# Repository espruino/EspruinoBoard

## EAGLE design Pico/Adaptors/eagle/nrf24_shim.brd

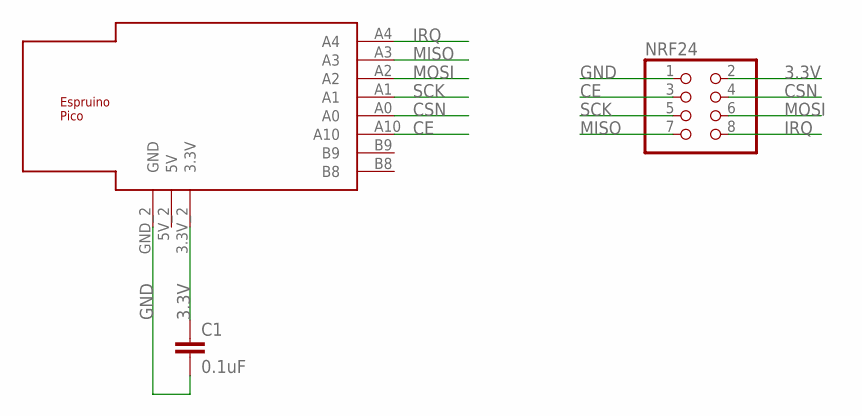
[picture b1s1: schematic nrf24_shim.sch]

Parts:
C1: 0.1uF; C1206
NRF24: PINHD-2X4; 2X04
U$1: ESPRUINO_PICO_0.05_SMALL

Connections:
3.3V: C1.1, NRF24.2, U$1.3.3V_2 (3.3V)
CE: NRF24.3, U$1.A10
CSN: NRF24.4, U$1.A0
GND: C1.2, NRF24.1, U$1.GND_2 (GND)
IRQ: NRF24.8, U$1.A4
MISO: NRF24.7, U$1.A3
MOSI: NRF24.6, U$1.A2
SCK: NRF24.5, U$1.A1

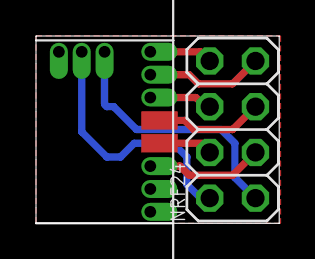
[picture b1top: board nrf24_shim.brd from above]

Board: 2 copper layers, 13.5 x 10.4 mm, 3 parts (1 on the bottom side), 8 nets.

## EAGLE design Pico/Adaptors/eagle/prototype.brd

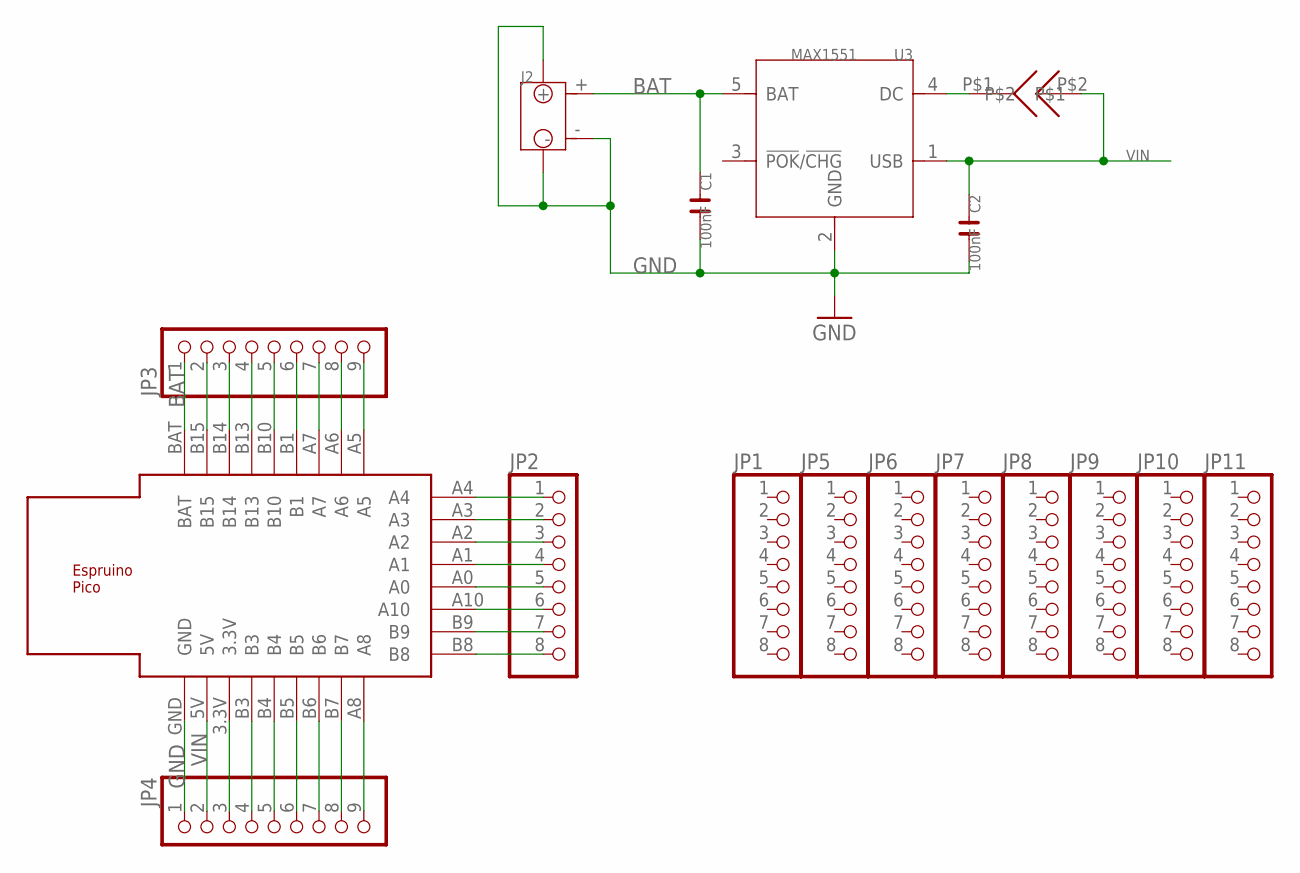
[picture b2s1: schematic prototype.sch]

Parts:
C1, C2: 100nF; C0603
J2: JST-2P-SMD-PW-3410050P1; 2P-SMD-2.0-90D
JP1, JP2, JP5, JP6, JP7, JP8, JP9, JP10, JP11: PINHD-1X08_2.54-S; 1X08-S
JP3, JP4: PINHD-1X09_2.54-S; 1X09-S
U3: MAX1551; SOT23-5
U$1: ESPRUINO_PICO_SMD
U$4: SOLDERJUMPER

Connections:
BAT: C1.1, J2.+, JP3.1, U3.5 (BAT), U$1.BAT
GND: C1.2, C2.2, J2.3, J2.4, J2.-, JP4.1, U3.2 (GND), U$1.GND
unnamed: JP2.2, U$1.A3
unnamed: JP2.3, U$1.A2
unnamed: JP2.4, U$1.A1
unnamed: JP2.5, U$1.A0
unnamed: JP2.6, U$1.A10
unnamed: JP2.7, U$1.B9
unnamed: JP4.3, U$1.3.3V
unnamed: JP4.4, U$1.B3
unnamed: JP2.8, U$1.B8
unnamed: JP4.5, U$1.B4
unnamed: JP4.6, U$1.B5
unnamed: JP4.7, U$1.B6
unnamed: JP4.8, U$1.B7
unnamed: JP4.9, U$1.A8
unnamed: JP3.2, U$1.B15
unnamed: JP3.3, U$1.B14
unnamed: JP3.4, U$1.B13
unnamed: JP3.5, U$1.B10
unnamed: JP3.6, U$1.B1
unnamed: JP3.7, U$1.A7
unnamed: JP3.8, U$1.A6
unnamed: JP3.9, U$1.A5
unnamed: JP2.1, U$1.A4
unnamed: U3.4 (DC), U$4.P$1
VIN: C2.1, JP4.2, U3.1 (USB), U$1.5V, U$4.P$2

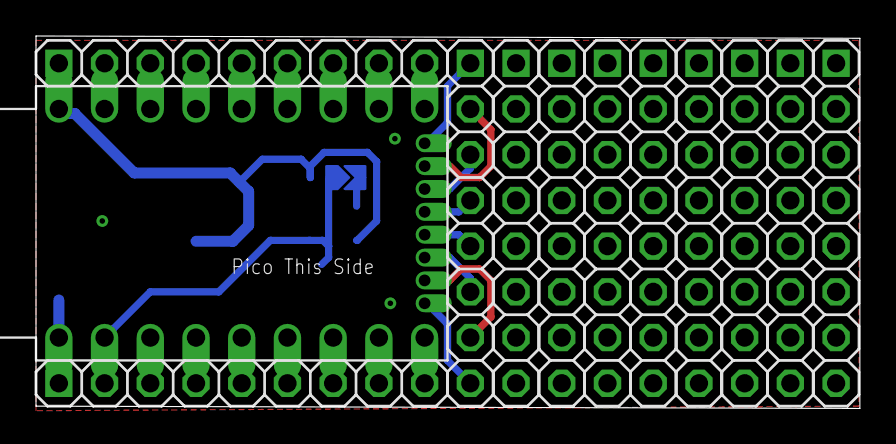
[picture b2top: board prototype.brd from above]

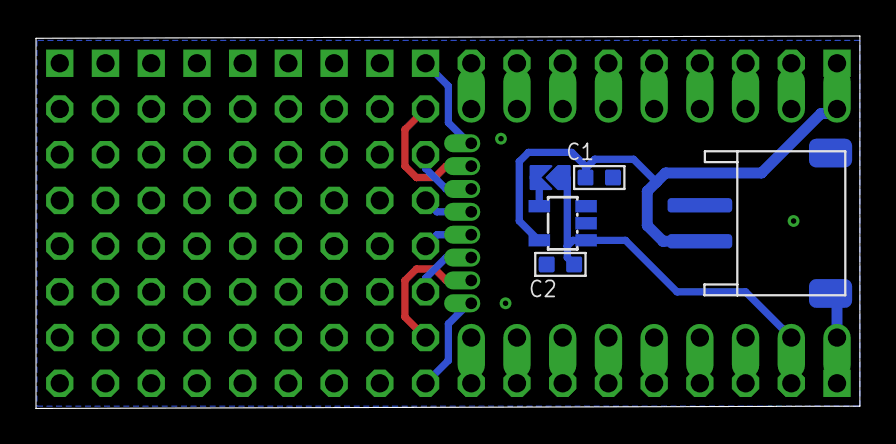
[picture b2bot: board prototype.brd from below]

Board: 2 copper layers, 45.8 x 20.7 mm, 17 parts (5 on the bottom side), 27 nets.

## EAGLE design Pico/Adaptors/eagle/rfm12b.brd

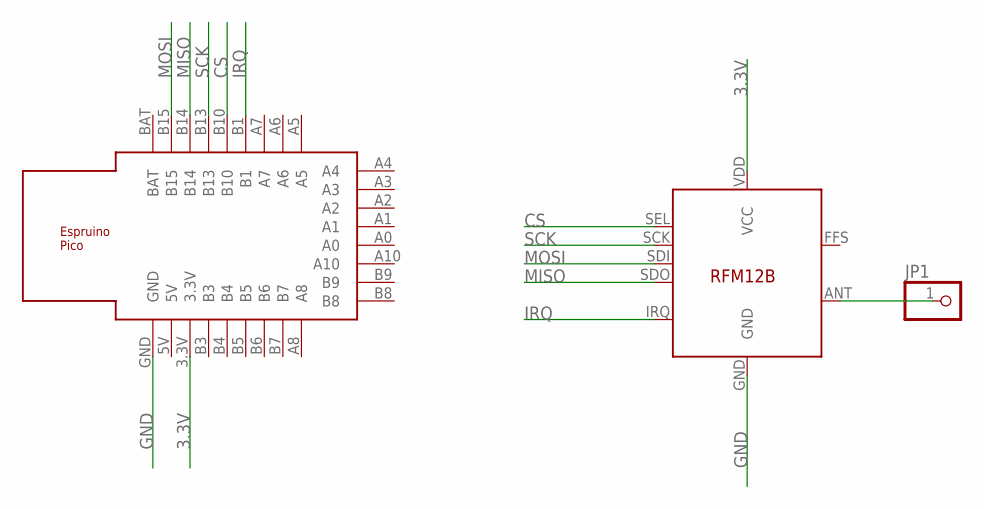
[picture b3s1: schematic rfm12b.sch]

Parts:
JP1: PINHD-1X1; 1X01
U$1: ESPRUINO_PICO_SMDONLY
U$2: RFM12B

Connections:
3.3V: U$1.3.3V, U$2.VDD (VCC)
CS: U$1.B10, U$2.SEL
GND: U$1.GND, U$2.GND
IRQ: U$1.B1, U$2.IRQ
MISO: U$1.B14, U$2.SDO
MOSI: U$1.B15, U$2.SDI
unnamed: JP1.1, U$2.ANT
SCK: U$1.B13, U$2.SCK

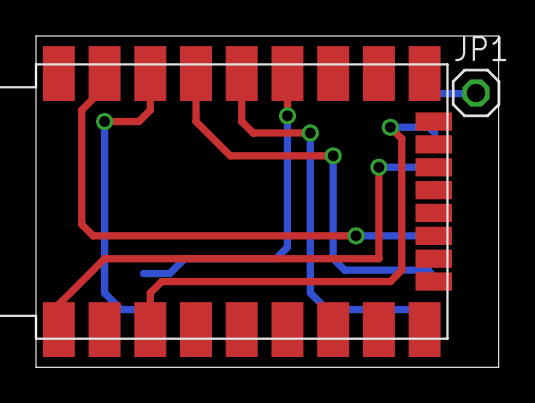
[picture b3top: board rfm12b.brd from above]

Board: 2 copper layers, 25.7 x 18.4 mm, 3 parts (1 on the bottom side), 8 nets.

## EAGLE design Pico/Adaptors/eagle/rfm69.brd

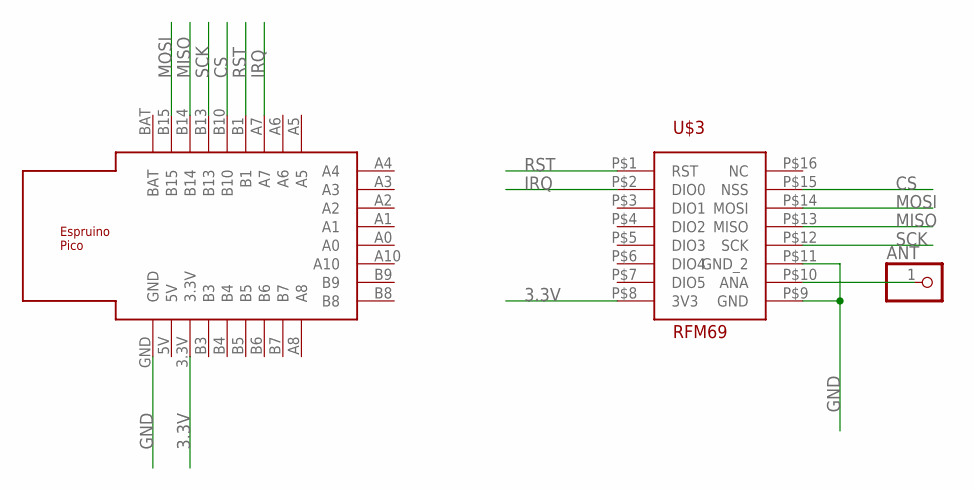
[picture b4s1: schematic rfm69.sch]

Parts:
ANT: PINHD-1X1; 1X01
U$1: ESPRUINO_PICO_SMDONLY
U$3: RFM69

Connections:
3.3V: U$1.3.3V, U$3.P$8 (3V3)
CS: U$1.B10, U$3.P$15 (NSS)
GND: U$1.GND, U$3.P$9 (GND), U$3.P$11 (GND_2)
IRQ: U$1.A7, U$3.P$2 (DIO0)
MISO: U$1.B14, U$3.P$13 (MISO)
MOSI: U$1.B15, U$3.P$14 (MOSI)
unnamed: ANT.1, U$3.P$10 (ANA)
RST: U$1.B1, U$3.P$1 (RST)
SCK: U$1.B13, U$3.P$12 (SCK)

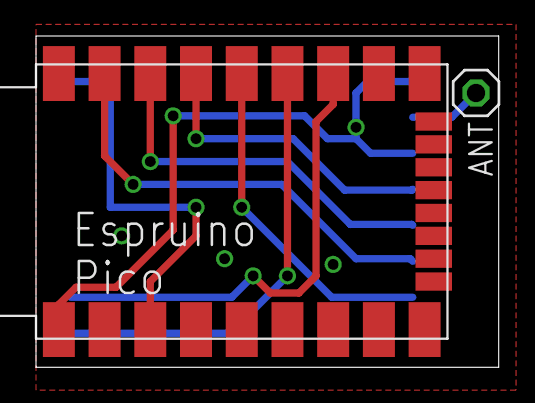
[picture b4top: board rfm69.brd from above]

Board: 2 copper layers, 25.7 x 18.4 mm, 3 parts (1 on the bottom side), 9 nets.

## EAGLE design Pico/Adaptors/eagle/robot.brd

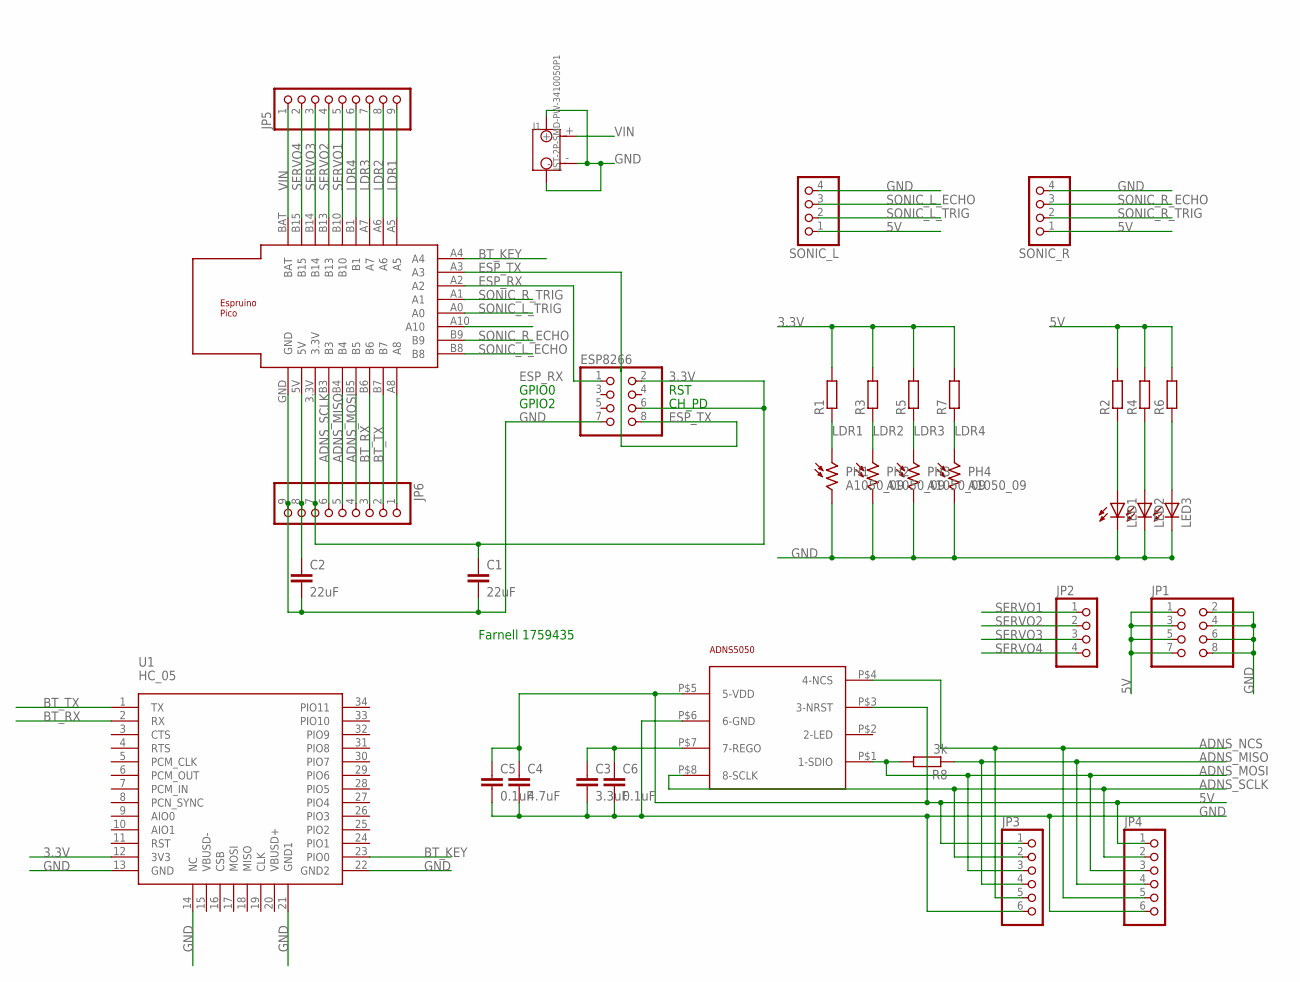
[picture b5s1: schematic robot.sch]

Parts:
C1, C2: 22uF; C1210
C3: 3.3uF; C1206
C4: 4.7uF; C1206
C5, C6: 0.1uF; C1206
ESP8266: PINHD-2X4; 2X04
J1: JST-2P-SMD-PW-3410050P1; 2P-SMD-2.0-90D
JP1: PINHD-2X4; 2X04
JP2: PINHD-1X4; 1X04
JP3, JP4: PINHD-1X6; 1X06
JP5, JP6: PINHD-1X9; 1X09
LED1, LED2, LED3: LED5MM
PH1, PH2, PH3, PH4: A1050_09; T0-46-A10XX
R1, R2, R3, R4, R5, R6, R7: R-EU_R1206; R1206
R8: 3k; R1206
SONIC_L: PINHD-1X4; 1X04
SONIC_R: PINHD-1X4; 1X04
U1: HC_05; BLUETOOTH_SMD
U$1: ESPRUINO_PICO_HALFSMD
U$2: ADNS5050; ADNS-5050

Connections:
3.3V: C1.1, ESP8266.2, ESP8266.6, JP6.7, R1.2, R3.2, R5.2, R7.2, U1.12 (3V3), U$1.3.3V
5V: C2.1, C4.1, C5.1, JP1.1, JP1.3, JP1.5, JP1.7, JP3.1, JP4.1, JP6.8, R2.2, R4.2, R6.2, SONIC_L.1, SONIC_R.1, U$1.5V, U$2.P$3 (3-NRST), U$2.P$5 (5-VDD)
ADNS_MISO: JP3.4, JP4.4, JP6.5, R8.1, U$1.B4
ADNS_MOSI: JP3.3, JP4.3, JP6.4, R8.2, U$1.B5, U$2.P$1 (1-SDIO)
ADNS_NCS: JP3.5, JP4.5, U$1.A10, U$2.P$4 (4-NCS)
ADNS_SCLK: JP3.2, JP4.2, JP6.6, U$1.B3, U$2.P$8 (8-SCLK)
BT_KEY: U1.23 (PIO0), U$1.A4
BT_RX: JP6.3, U1.2 (RX), U$1.B6
BT_TX: JP6.2, U1.1 (TX), U$1.B7
ESP_RX: ESP8266.1, U$1.A2
ESP_TX: ESP8266.8, U$1.A3
GND: C1.2, C2.2, C3.2, C4.2, C5.2, C6.2, ESP8266.7, J1.3, J1.4, J1.-, JP1.2, JP1.4, JP1.6, JP1.8, JP3.6, JP4.6, JP6.9, LED1.K (C), LED2.K (C), LED3.K (C), PH1.2, PH2.2, PH3.2, PH4.2, SONIC_L.4, SONIC_R.4, U1.13 (GND), U1.14 (NC), U1.21 (GND1), U1.22 (GND2), U$1.GND, U$2.P$6 (6-GND)
LDR1: JP5.9, PH1.1, R1.1, U$1.A5
LDR2: JP5.8, PH2.1, R3.1, U$1.A6
LDR3: JP5.7, PH3.1, R5.1, U$1.A7
LDR4: JP5.6, PH4.1, R7.1, U$1.B1
unnamed: JP6.1, U$1.A8
unnamed: C3.1, C6.1, U$2.P$7 (7-REGO)
unnamed: LED3.A, R6.1
unnamed: LED2.A, R4.1
unnamed: LED1.A, R2.1
SERVO1: JP2.1, JP5.5, U$1.B10
SERVO2: JP2.2, JP5.4, U$1.B13
SERVO3: JP2.3, JP5.3, U$1.B14
SERVO4: JP2.4, JP5.2, U$1.B15
SONIC_L_ECHO: SONIC_L.3, U$1.B8
SONIC_L_TRIG: SONIC_L.2, U$1.A0
SONIC_R_ECHO: SONIC_R.3, U$1.B9
SONIC_R_TRIG: SONIC_R.2, U$1.A1
VIN: J1.+, JP5.1, U$1.BAT

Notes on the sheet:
CH_PD
RST
GPIO0
GPIO2
Farnell 1759435

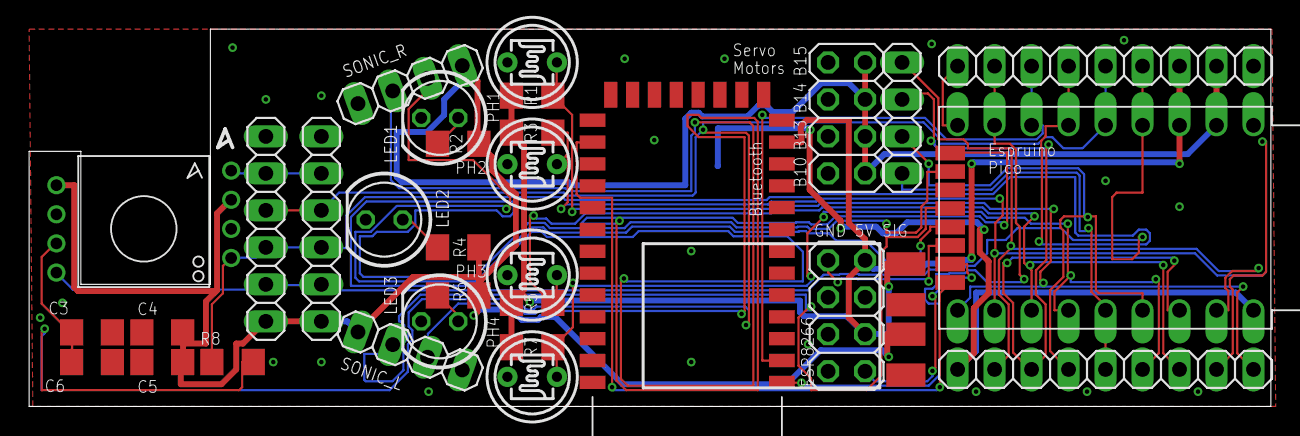
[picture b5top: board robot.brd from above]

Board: 2 copper layers, 85.3 x 25.9 mm, 34 parts (1 on the bottom side), 30 nets.

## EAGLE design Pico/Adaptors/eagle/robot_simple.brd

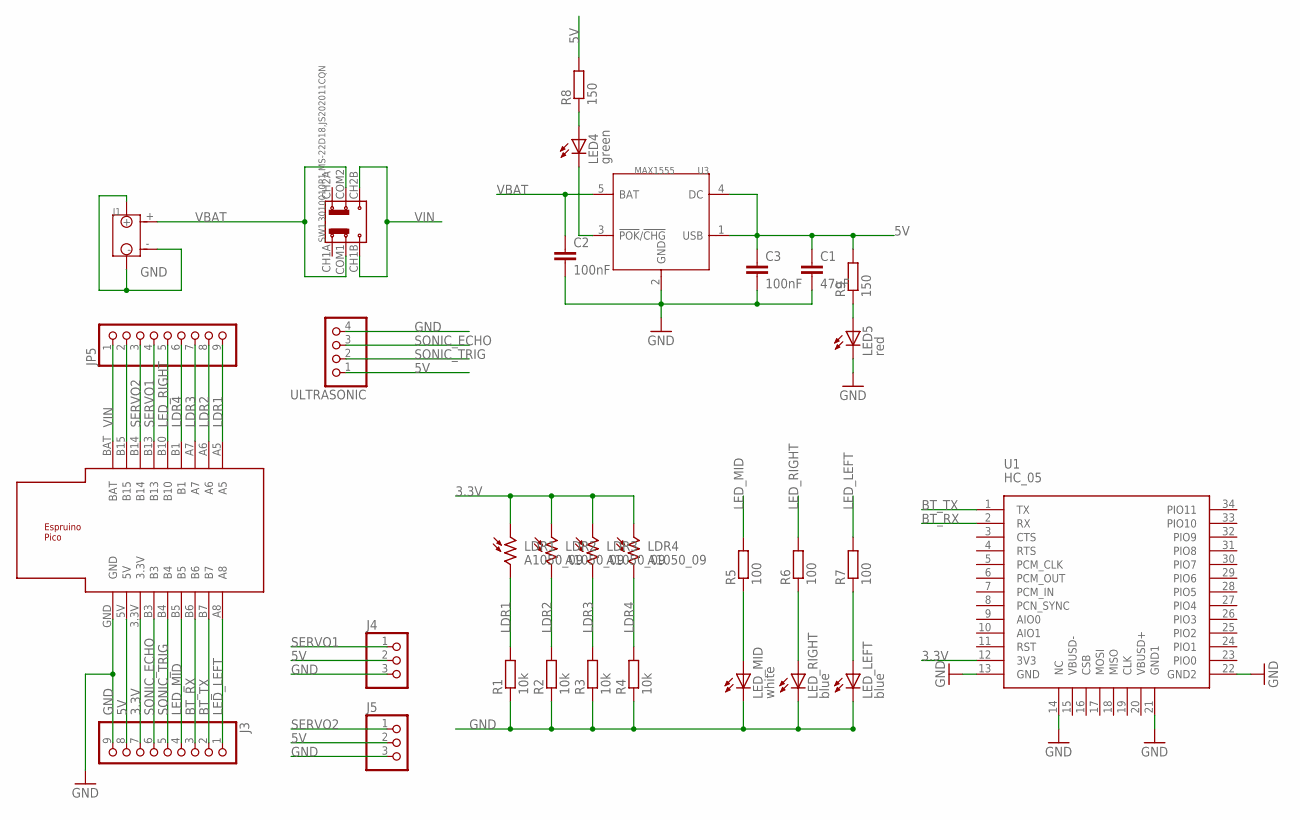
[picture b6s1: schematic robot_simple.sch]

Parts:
C1: 47uF; C1210
C2, C3: 100nF; C0805
J1: JST-2P-SMD-PW-3410050P1; 2P-SMD-2.0-90D
J3: PINHD-1X9; 1X09
J4, J5: PINHD-1X3; 1X03
JP5: PINHD-1X9; 1X09
LDR1, LDR2, LDR3, LDR4: A1050_09; T0-46-A10XX
LED4: green; CHIP-LED0805
LED5: red; CHIP-LED0805
LED_LEFT: blue; CHIP-LED0805
LED_MID: white; LED10MM
LED_RIGHT: blue; CHIP-LED0805
R1, R2, R3, R4: 10k; R0805
R5, R6, R7: 100; R0805
R8, R9: 150; R0805
SW1: 3010010P1,MS-22D18,JS202011CQN; 6P-2CH-2.54-9.1X3.5X3.2+2H
U1: HC_05; BLUETOOTH_SMD
U3: MAX1555; SOT23-5
U$1: ESPRUINO_PICO_0.1
ULTRASONIC: PINHD-1X4; 1X04

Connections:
3.3V: J3.7, LDR1.1, LDR2.1, LDR3.1, LDR4.1, U1.12 (3V3), U$1.3.3V
5V: C1.1, C3.1, J3.8, J4.2, J5.2, R8.2, R9.2, U3.1 (USB), U3.4 (DC), U$1.5V, ULTRASONIC.1
BT_RX: J3.3, U1.2 (RX), U$1.B6
BT_TX: J3.2, U1.1 (TX), U$1.B7
GND: C1.2, C2.2, C3.2, J1.3, J1.4, J1.-, J3.9, J4.3, J5.3, LED5.C, LED_LEFT.C, LED_MID.K (C), LED_RIGHT.C, R1.1, R2.1, R3.1, R4.1, U1.13 (GND), U1.14 (NC), U1.21 (GND1), U1.22 (GND2), U3.2 (GND), U$1.GND, ULTRASONIC.4
LDR1: JP5.9, LDR1.2, R1.2, U$1.A5
LDR2: JP5.8, LDR2.2, R2.2, U$1.A6
LDR3: JP5.7, LDR3.2, R3.2, U$1.A7
LDR4: JP5.6, LDR4.2, R4.2, U$1.B1
LED_LEFT: J3.1, R7.2, U$1.A8
LED_MID: J3.4, R5.2, U$1.B5
LED_RIGHT: JP5.5, R6.2, U$1.B10
unnamed: JP5.2, U$1.B15
unnamed: LED_LEFT.A, R7.1
unnamed: LED_RIGHT.A, R6.1
unnamed: LED_MID.A, R5.1
unnamed: LED4.C, U3.3 (!POK!/!CHG!)
unnamed: LED4.A, R8.1
unnamed: LED5.A, R9.1
SERVO1: J4.1, JP5.4, U$1.B13
SERVO2: J5.1, JP5.3, U$1.B14
SONIC_ECHO: J3.6, U$1.B3, ULTRASONIC.3
SONIC_TRIG: J3.5, U$1.B4, ULTRASONIC.2
VBAT: C2.1, J1.+, SW1.COM1, SW1.COM2, U3.5 (BAT)
VIN: JP5.1, SW1.CH1B, SW1.CH2B, U$1.BAT

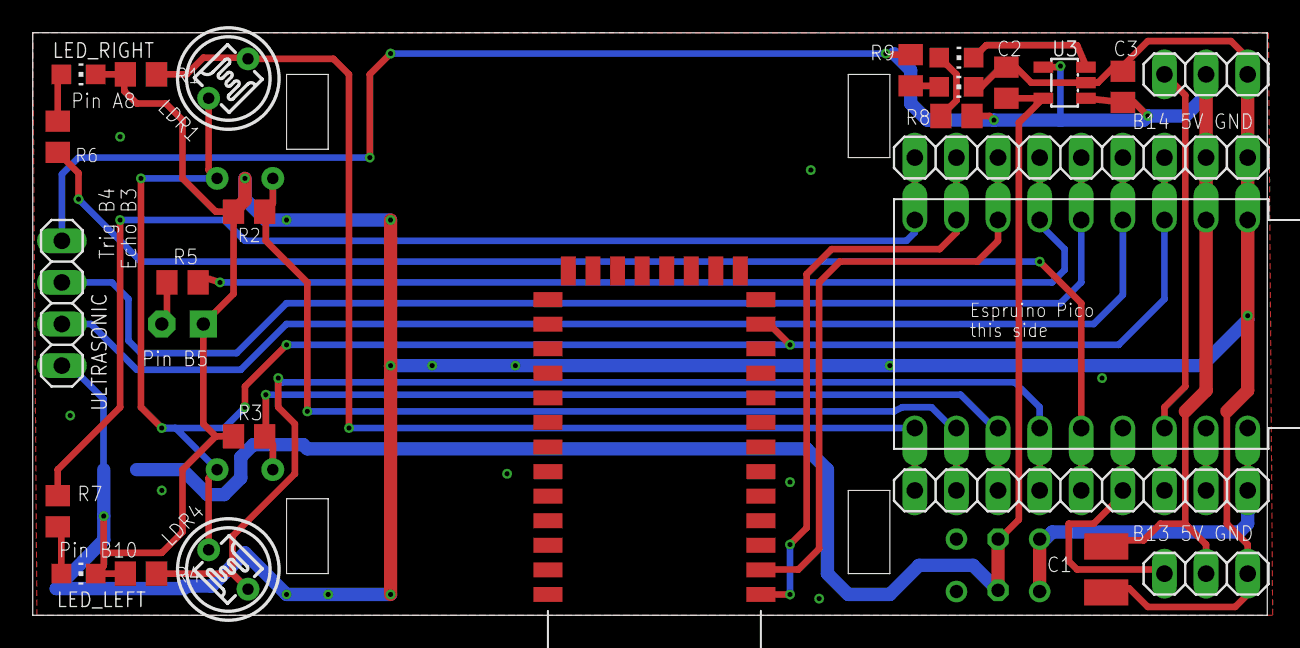
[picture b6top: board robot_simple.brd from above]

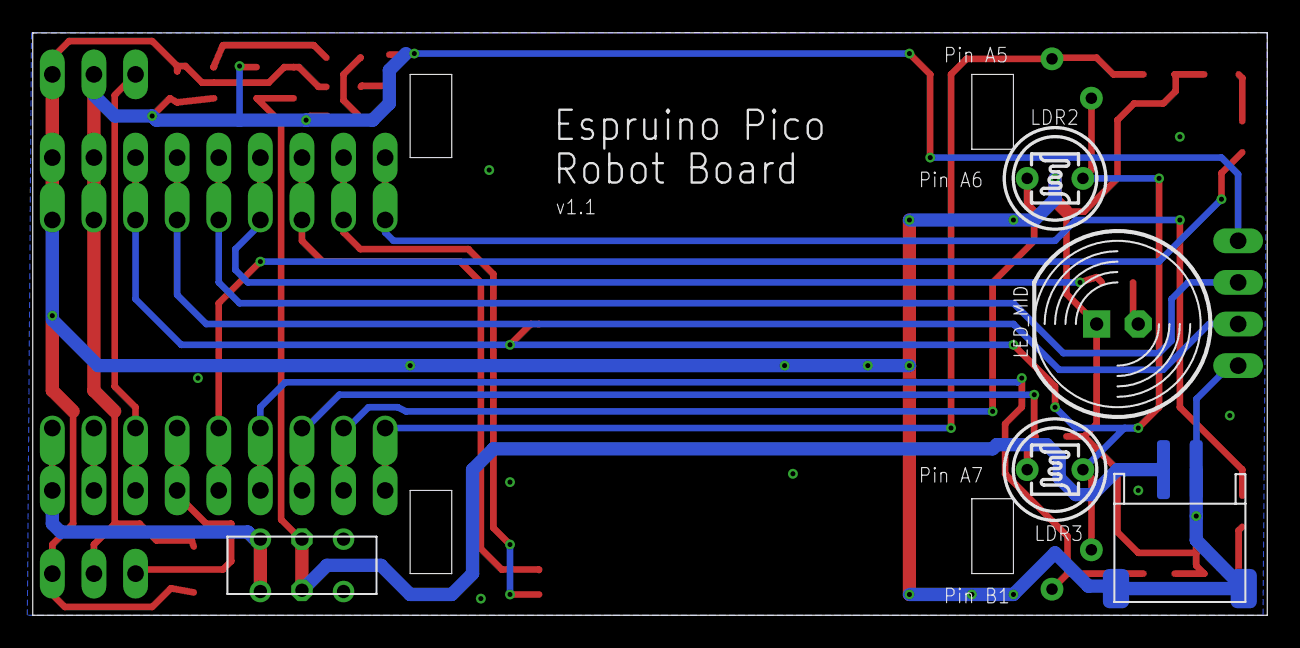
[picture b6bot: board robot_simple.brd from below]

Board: 2 copper layers, 75.4 x 35.6 mm, 31 parts (5 on the bottom side), 25 nets.

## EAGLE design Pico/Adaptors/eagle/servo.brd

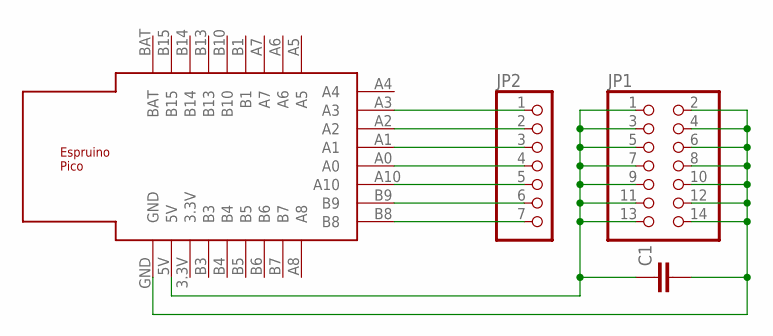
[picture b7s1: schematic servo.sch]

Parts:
C1: C-EUC1210; C1210
JP1: PINHD-2X7; 2X07
JP2: PINHD-1X7; 1X07
U$1: ESPRUINO_PICO_SMD

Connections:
5V: C1.1, JP1.1, JP1.3, JP1.5, JP1.7, JP1.9, JP1.11, JP1.13, U$1.5V
GND: C1.2, JP1.2, JP1.4, JP1.6, JP1.8, JP1.10, JP1.12, JP1.14, U$1.GND
unnamed: JP2.1, U$1.A3
unnamed: JP2.2, U$1.A2
unnamed: JP2.3, U$1.A1
unnamed: JP2.4, U$1.A0
unnamed: JP2.5, U$1.A10
unnamed: JP2.6, U$1.B9
unnamed: JP2.7, U$1.B8

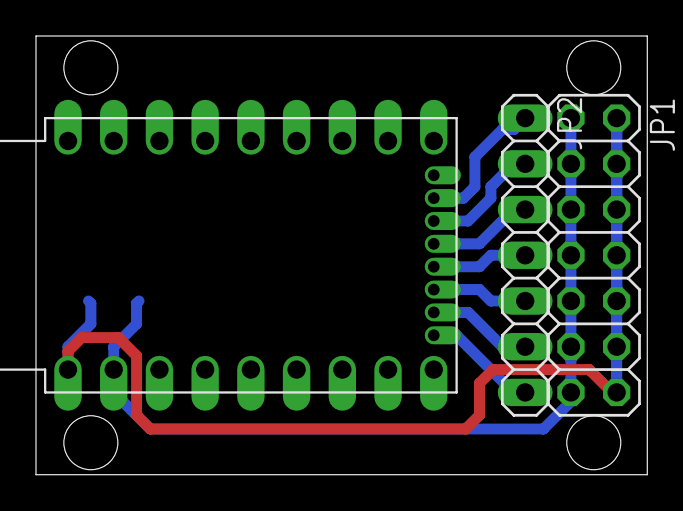
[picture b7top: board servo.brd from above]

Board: 2 copper layers, 34.0 x 24.4 mm, 4 parts (1 on the bottom side), 9 nets.
